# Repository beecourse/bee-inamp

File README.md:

bee-inamp
=========

This [bee](https://github.com/beecourse) provides an **in**strumentation **amp**lifier with adjustable gain.

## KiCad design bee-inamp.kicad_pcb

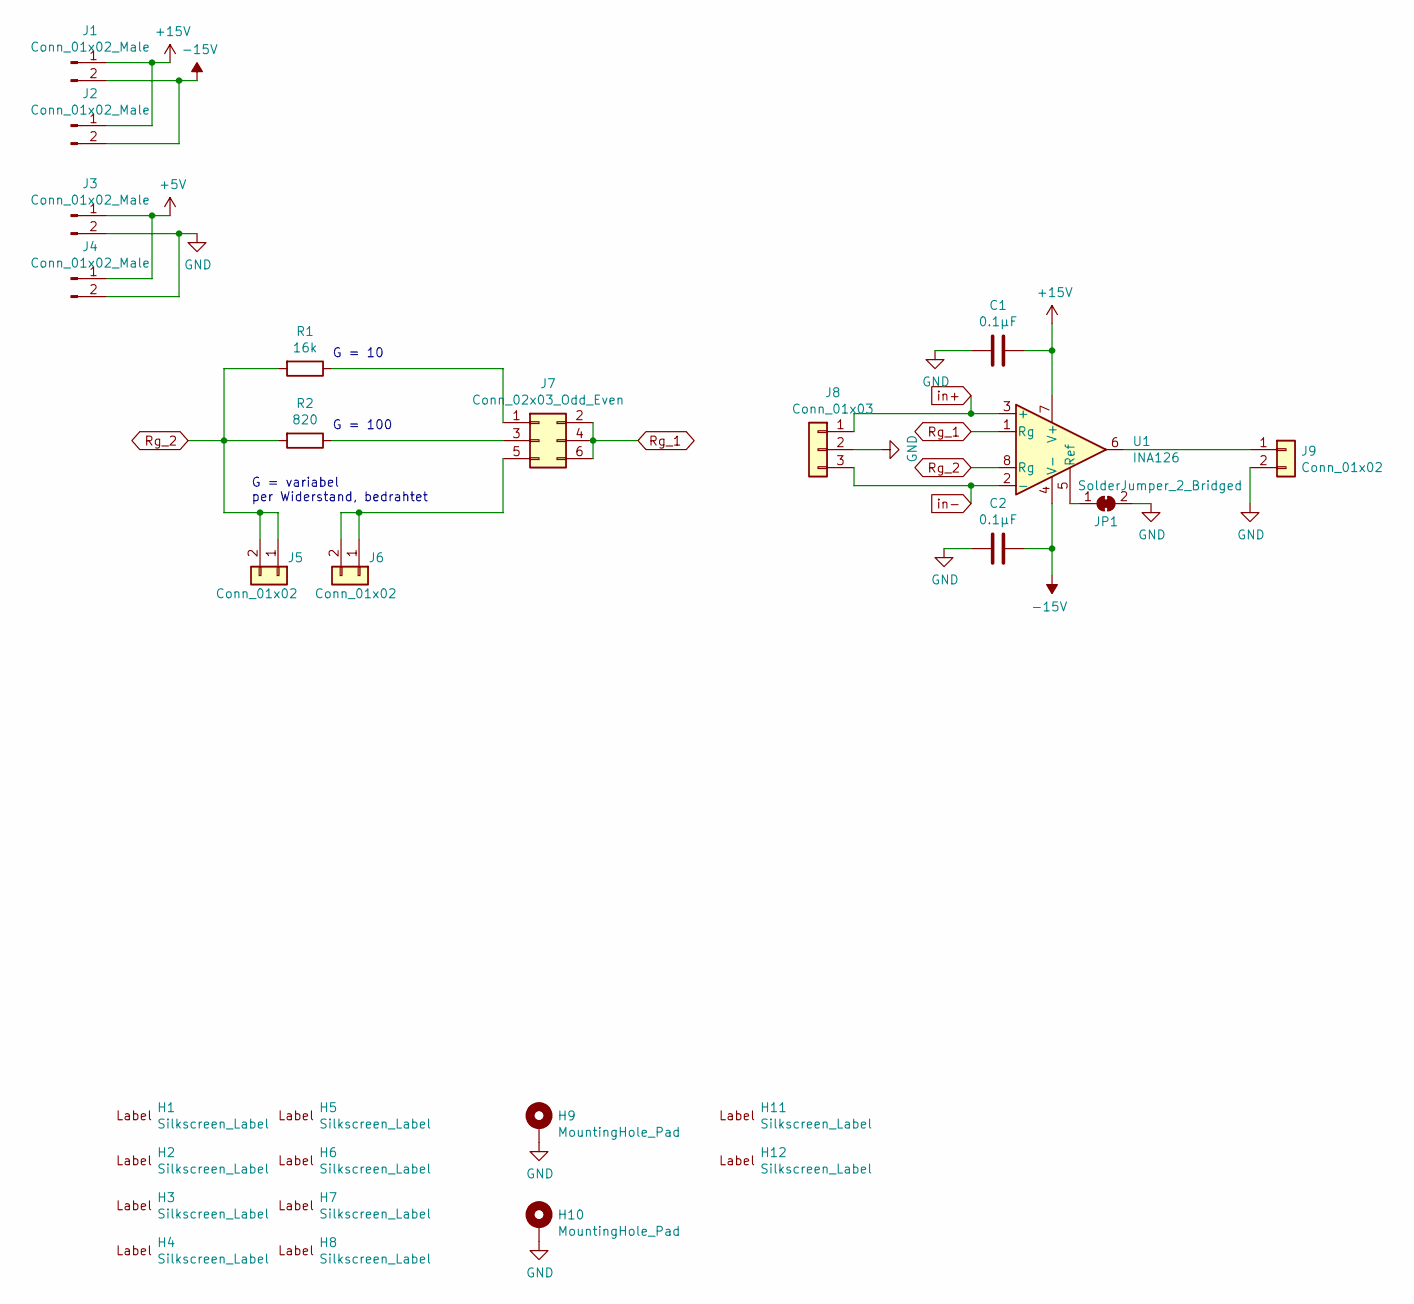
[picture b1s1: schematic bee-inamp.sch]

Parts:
C1, C2: 0.1µF; C_0805_2012Metric_Pad1.15x1.40mm_HandSolder
H1, H2: Silkscreen_Label; Text_U_B+_Silkscreen
H3, H4: Silkscreen_Label; Text_U_B-_Silkscreen
H5, H6: Silkscreen_Label; Text_U_B2_Silkscreen
H7, H8: Silkscreen_Label; Symbol_GND_Silkscreen
H9, H10: MountingHole_Pad; MountingHole_3.2mm_M3_ISO7380_Pad
H11: Silkscreen_Label; EMT-Logo_5.1x2.5mm_Silkscreen
H12: Silkscreen_Label; BEE-Logo_Silkscreen_small
J1, J2, J3, J4: Conn_01x02_Male; PinHeader_1x02_P2.54mm_Vertical
J5, J6: Conn_01x02; PinSocket_1x02_P2.54mm_Vertical
J7: Conn_02x03_Odd_Even; PinHeader_2x03_P2.54mm_Vertical_SMD
J8: Conn_01x03; PinHeader_1x03_P2.54mm_Vertical
J9: Conn_01x02; PinHeader_1x02_P2.54mm_Vertical
JP1: SolderJumper_2_Bridged; SolderJumper-2_P1.3mm_Bridged_Pad1.0x1.5mm
R1: 16k; R_0805_2012Metric_Pad1.15x1.40mm_HandSolder
R2: 820; R_0805_2012Metric_Pad1.15x1.40mm_HandSolder
U1: INA126; SOIC-8_3.9x4.9mm_P1.27mm

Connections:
+5V: J3.1, J4.1
+15V: C1.1, J1.1, J2.1, U1.7 (V+)
-15V: C2.1, J1.2, J2.2, U1.4 (V-)
GND: C1.2, C2.2, H9.1, H10.1, J3.2, J4.2, J8.2, J9.2, JP1.2 (B)
unnamed: J6.1, J6.2, J7.5
unnamed: J7.1, R1.1
unnamed: J7.3, R2.1
unnamed: J9.1, U1.6
unnamed: JP1.1 (A), U1.5 (Ref)
Rg_1: J7.2, J7.4, J7.6, U1.1 (Rg)
Rg_2: J5.1, J5.2, R1.2, R2.2, U1.8 (Rg)
in+: J8.1, U1.3 (+)
in-: J8.3, U1.2 (-)

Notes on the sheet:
G = 10
G = 100
G = variabel per Widerstand, bedrahtet

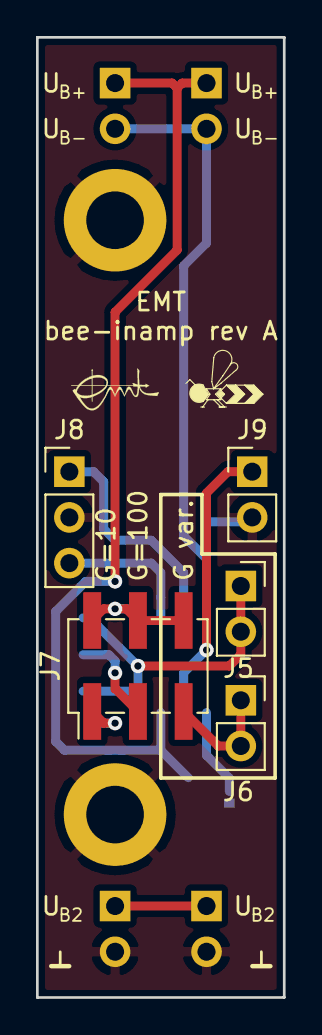
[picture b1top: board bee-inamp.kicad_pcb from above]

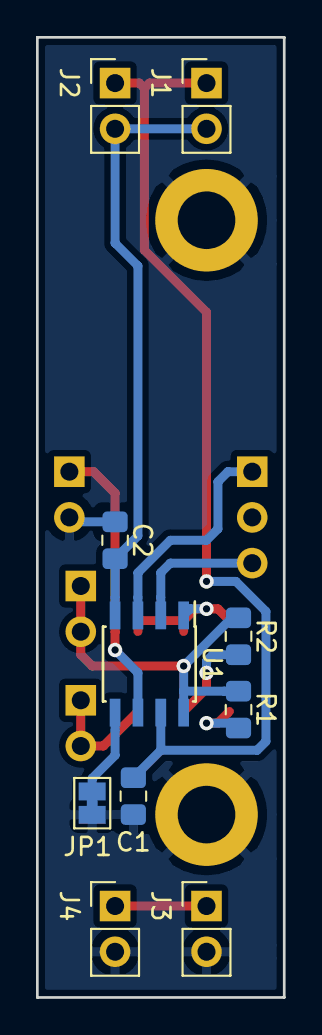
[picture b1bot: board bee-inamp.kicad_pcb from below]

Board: 2 copper layers, 13.7 x 53.3 mm, 27 parts (10 on the bottom side), 13 nets.

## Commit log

2019-04-23 first commit - empty project
2019-04-23 add gitignore
2019-04-26 schematic and layout
2019-04-29 Place refs on silkscreen.
2019-04-30 Add labels for G.
2019-04-30 Update labels and mounting holes.
2019-04-30 Update gitignore.
2019-05-03 Update ground planes.
2019-05-03 DRC - remove unnecessary via.
2019-05-03 Add text and logos.
2019-05-07 Add part numbers.
2019-05-22 Fix order number (THT->SMD).
2019-07-17 Replace SO package by SOIC. Fixes #1.
2020-07-01 Relabel as bee specific.
2020-07-15 Add license.
2020-07-15 Add readme.
2023-03-17 Add figure showing top view of PCB
